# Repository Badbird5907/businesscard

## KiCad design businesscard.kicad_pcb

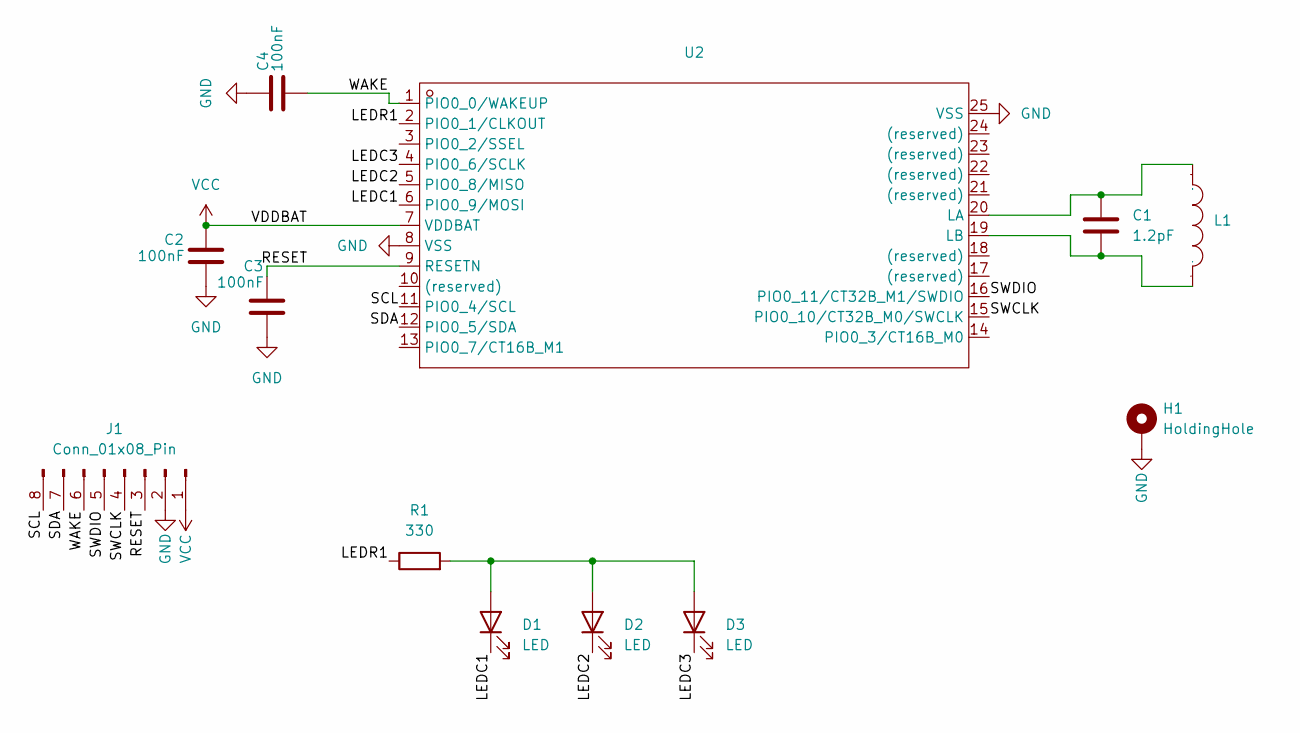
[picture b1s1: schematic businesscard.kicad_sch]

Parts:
C1: 1.2pF; C_0201_0603Metric
C2, C3, C4: 100nF; C_0402_1005Metric
D1, D2, D3: LED; LED_1206_3216Metric
H1: HoldingHole
J1: Conn_01x08_Pin; 8-Pin-Pads
L1: 25X48MM_NFC_EXPOSED_ANTENNA
R1: 330; R_0402_1005Metric
U2: NXP LPC8N04FHI24E; Manufacturer Part LPC8N04FHI24E; LCSC Part Name LPC8N04FHI24E

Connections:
/LEDC1: D1.1 (K), U2.6 (PIO0_9/MOSI)
/LEDC2: D2.1 (K), U2.5 (PIO0_8/MISO)
/LEDC3: D3.1 (K), U2.4 (PIO0_6/SCLK)
/LEDR1: R1.1, U2.2 (PIO0_1/CLKOUT)
/RESET: C3.1, J1.3, U2.9 (RESETN)
/SCL: J1.8, U2.11 (PIO0_4/SCL)
/SDA: J1.7, U2.12 (PIO0_5/SDA)
/SWCLK: J1.4, U2.15 (PIO0_10/CT32B_M0/SWCLK)
/SWDIO: J1.5, U2.16 (PIO0_11/CT32B_M1/SWDIO)
/WAKE: C4.1, J1.6, U2.1 (PIO0_0/WAKEUP)
GND: C2.2, C3.2, C4.2, H1.1, J1.2, U2.8 (VSS), U2.25 (VSS)
unnamed: D1.2 (A), D2.2 (A), D3.2 (A), R1.2
unnamed: C1.1, L1.1, U2.20 (LA)
unnamed: C1.2, L1.2, U2.19 (LB)
VCC: C2.1, J1.1, U2.7 (VDDBAT)

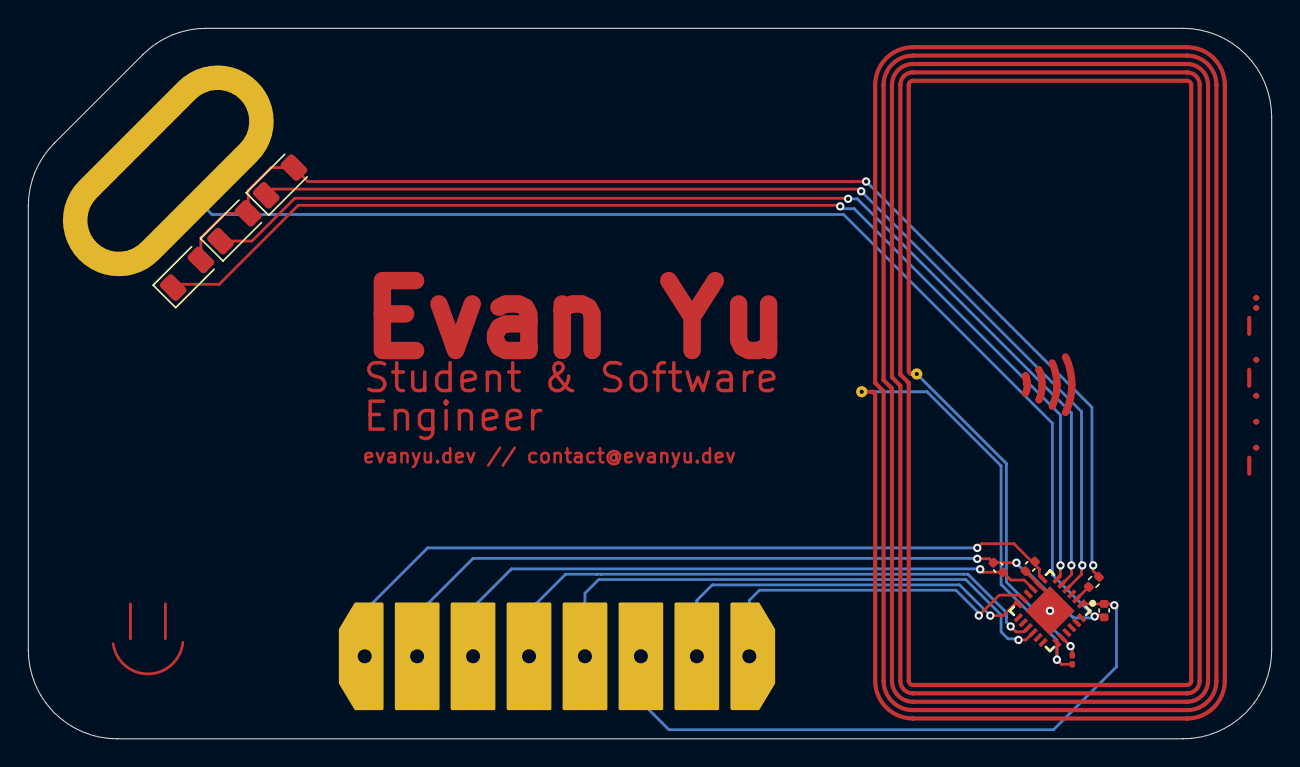
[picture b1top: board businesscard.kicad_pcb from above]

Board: 2 copper layers, 88.9 x 50.8 mm, 12 parts (0 on the bottom side), 15 nets.

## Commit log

2025-02-22 stuff
2025-02-23 jdsifhkds
2025-02-24 update schematics and stuff
2025-02-24 add gitignore
2025-02-25 finish pcb routing
2025-02-26 update footprints and stuff
2025-03-26 finalize pcb
2025-05-09 business card stuff
